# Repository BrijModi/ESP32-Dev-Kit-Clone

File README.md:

# ESP32 Dev Kit Clone

A custom **2-layer ESP32 Dev Kit V1 (30-pin)** PCB designed in **KiCad 9.0**. This repository contains the complete hardware design, including the schematic, PCB layout, 3D model, and Bill of Materials (BOM).

---

## Features

- ESP32-WROOM-32 module
- 2-layer PCB
- Micro USB interface
- USB-to-UART programming circuit
- Automatic Boot & Reset circuitry
- 3.3V power supply
- GPIO breakout headers
- Complete KiCad project files
- Interactive Bill of Materials
- 3D STEP model

---

## PCB Preview

### Front

### Back

---

## PCB Specifications

| Parameter | Value |
|-----------|-------|
| PCB Size | 47.02 × 29.16 mm |
| Layers | 2 |
| Software | KiCad 9.0 |

---

## 📂 Repository Contents

- `View/` – PCB renders, 3D model, schematic PDF, and PCB preview PDF.
- `ESP32 Dev Kit.kicad_pro` – KiCad project file.
- `ESP32 Dev Kit.kicad_sch` – Main schematic.
- `ESP32 Dev Kit.kicad_pcb` – PCB layout.
- `Connectors.kicad_sch` – Connector schematic sheet.
- `BOM.html` – Interactive Bill of Materials.
- `.gitignore` – Git ignore configuration.

---

## Documentation

- 📄 **Schematic:** [Schematic_View.pdf](View/Schematic_View.pdf)
- 📋 **Bill of Materials:** [BOM.html](BOM.html)
- 📦 **3D Model:** `View/ESP32 Dev Kit.step`

---

## Getting Started

1. Clone the repository

```bash
git clone https://github.com/BrijModi/ESP32-Dev-Kit-Clone.git
```

2. Open `ESP32 Dev Kit.kicad_pro` using **KiCad 9.0**.

---

# 📌 Applications

- ESP32 hardware reference
- PCB design learning
- Custom ESP32 development board
- Embedded systems projects
- Educational purposes

---

## License

This project is released under the **MIT License**.

---

## Author

**Brij Modi**

GitHub: https://github.com/BrijModi

⭐ If you found this project useful, consider starring the repository.

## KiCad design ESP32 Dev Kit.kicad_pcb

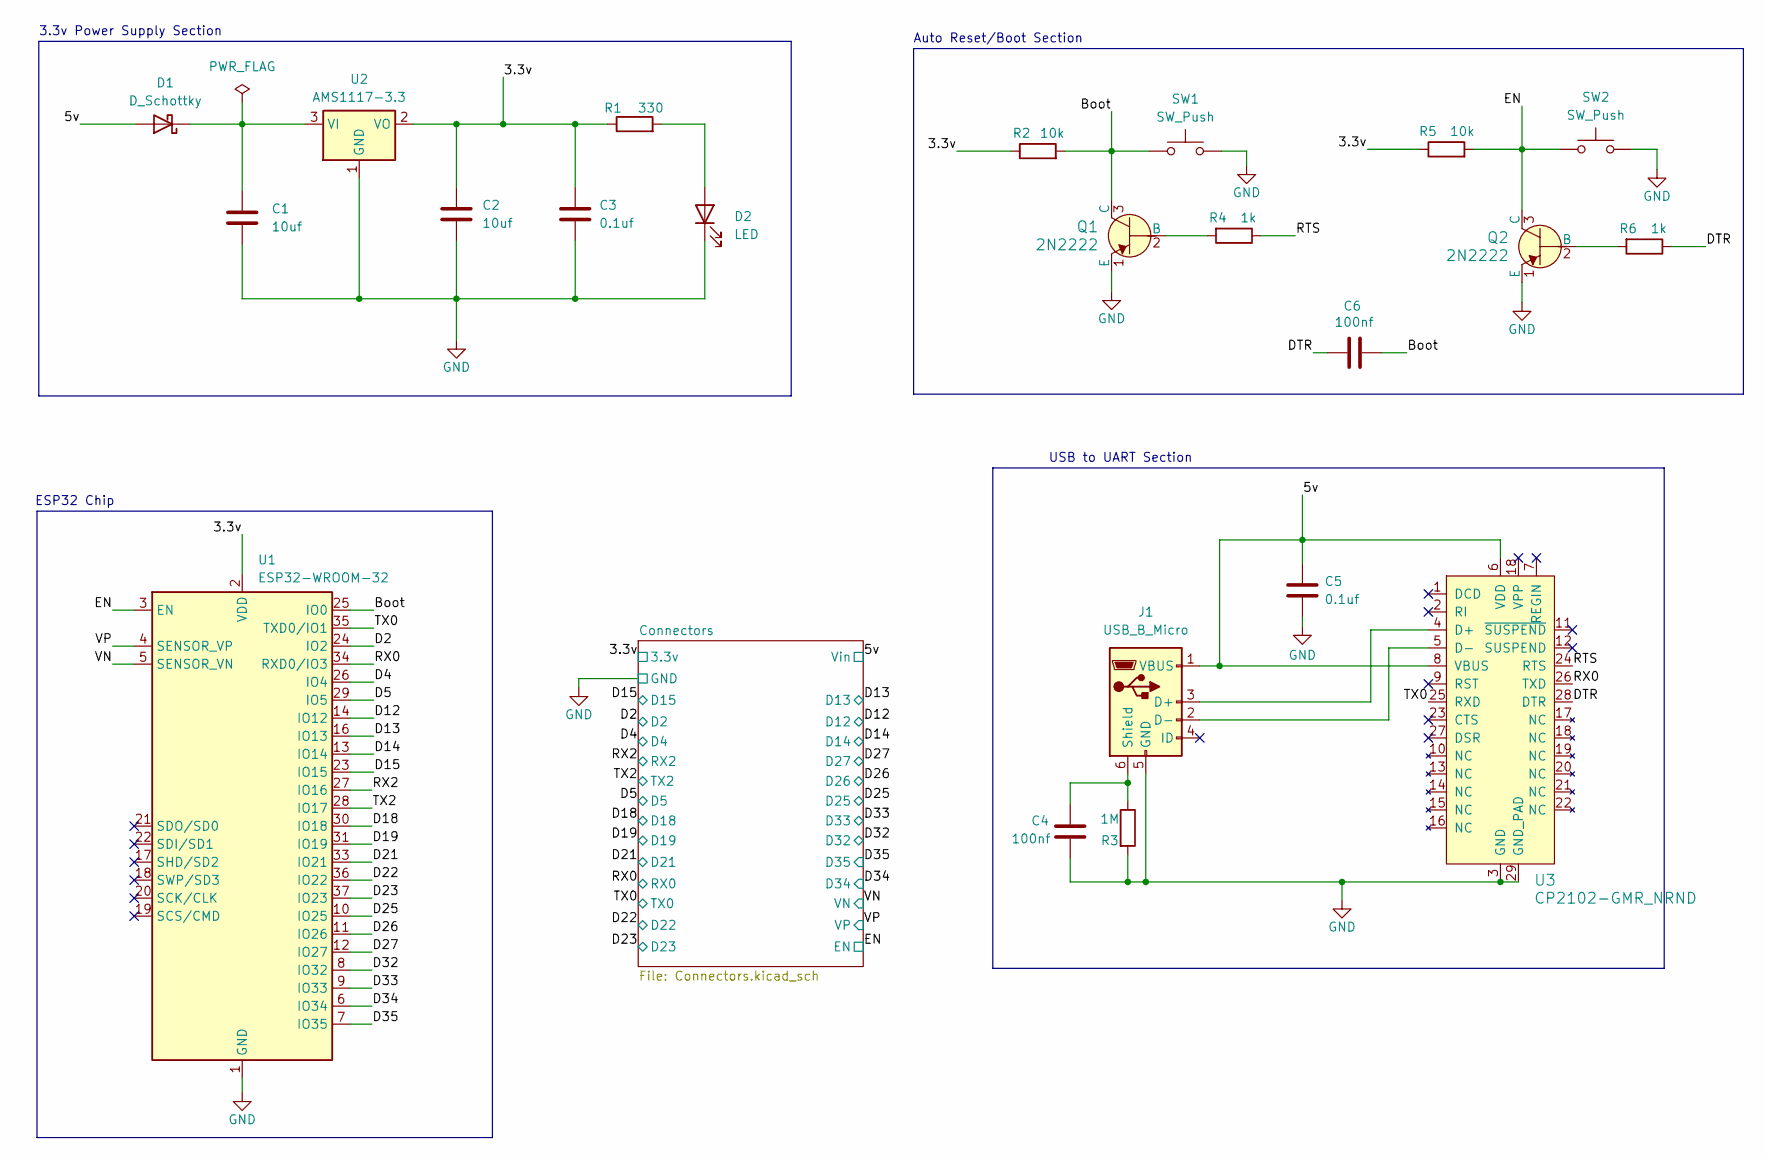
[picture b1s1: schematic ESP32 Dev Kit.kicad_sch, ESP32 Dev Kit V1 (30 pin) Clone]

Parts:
C1, C2: 10uf; C_0805_2012Metric_Pad1.18x1.45mm_HandSolder
C3, C5: 0.1uf; C_0805_2012Metric_Pad1.18x1.45mm_HandSolder
C4, C6: 100nf; C_0805_2012Metric_Pad1.18x1.45mm_HandSolder
D1: D_Schottky; D_SOD-123
D2: LED; LED_0805_2012Metric_Pad1.15x1.40mm_HandSolder
J1: USB_B_Micro; USB_Micro-B_Molex_47346-0001
Q1, Q2: 2N2222; SOT-23; MPN 2N2222; Digi-Key_PN 2N2222CS-ND
R1: 330; R_0805_2012Metric_Pad1.20x1.40mm_HandSolder
R2, R5: 10k; R_0805_2012Metric_Pad1.20x1.40mm_HandSolder
R3: 1M; R_0805_2012Metric_Pad1.20x1.40mm_HandSolder
R4, R6: 1k; R_0805_2012Metric_Pad1.20x1.40mm_HandSolder
SW1, SW2: SW_Push; SW_SPST_B3U-1000P
U1: ESP32-WROOM-32
U2: AMS1117-3.3; SOT-223-3_TabPin2
U3: CP2102-GMR_NRND; VFQFN-28-1EP_5x5mm; MPN CP2102-GMR; Digi-Key_PN 336-1160-1-ND

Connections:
/3.3v: C2.1, C3.1, R1.1, R2.1, R5.1, U1.2 (VDD), U2.2 (VO); also elsewhere on the board
/5v: C5.1, D1.2 (A), J1.1 (VBUS), U3.6 (VDD), U3.8 (VBUS); also elsewhere on the board
/Boot: C6.2, Q1.3 (C), R2.2, SW1.1, U1.25 (IO0)
/D2: U1.24 (IO2); also elsewhere on the board
/D4: U1.26 (IO4); also elsewhere on the board
/D5: U1.29 (IO5); also elsewhere on the board
/D12: U1.14 (IO12); also elsewhere on the board
/D13: U1.16 (IO13); also elsewhere on the board
/D14: U1.13 (IO14); also elsewhere on the board
/D15: U1.23 (IO15); also elsewhere on the board
/D18: U1.30 (IO18); also elsewhere on the board
/D19: U1.31 (IO19); also elsewhere on the board
/D21: U1.33 (IO21); also elsewhere on the board
/D22: U1.36 (IO22); also elsewhere on the board
/D23: U1.37 (IO23); also elsewhere on the board
/D25: U1.10 (IO25); also elsewhere on the board
/D26: U1.11 (IO26); also elsewhere on the board
/D27: U1.12 (IO27); also elsewhere on the board
/D32: U1.8 (IO32); also elsewhere on the board
/D33: U1.9 (IO33); also elsewhere on the board
/D34: U1.6 (IO34); also elsewhere on the board
/D35: U1.7 (IO35); also elsewhere on the board
/DTR: C6.1, R6.1, U3.28 (DTR)
/EN: Q2.3 (C), R5.2, SW2.1, U1.3 (EN); also elsewhere on the board
/RTS: R4.1, U3.24 (RTS)
/RX0: U1.34 (RXD0/IO3), U3.26 (TXD); also elsewhere on the board
/RX2: U1.27 (IO16); also elsewhere on the board
/TX0: U1.35 (TXD0/IO1), U3.25 (RXD); also elsewhere on the board
/TX2: U1.28 (IO17); also elsewhere on the board
/VN: U1.5 (SENSOR_VN); also elsewhere on the board
/VP: U1.4 (SENSOR_VP); also elsewhere on the board
GND: C1.2, C2.2, C3.2, C4.2, C5.2, D2.1 (K), J1.5 (GND), Q1.1 (E), Q2.1 (E), R3.2, SW1.2, SW2.2, U1.1 (GND), U1.15 (GND), U1.38 (GND), U1.39 (GND), U2.1 (GND), U3.3 (GND), U3.29 (GND_PAD); also elsewhere on the board
unnamed: C1.1, D1.1 (K), U2.3 (VI)
unnamed: D2.2 (A), R1.2
unnamed: J1.3 (D+), U3.4 (D+)
unnamed: J1.2 (D-), U3.5 (D-)
unnamed: C4.1, J1.6 (Shield), R3.1
unnamed: Q1.2 (B), R4.2
unnamed: Q2.2 (B), R6.2

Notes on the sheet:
Auto Reset/Boot Section
3.3v Power Supply Section
USB to UART Section
ESP32 Chip

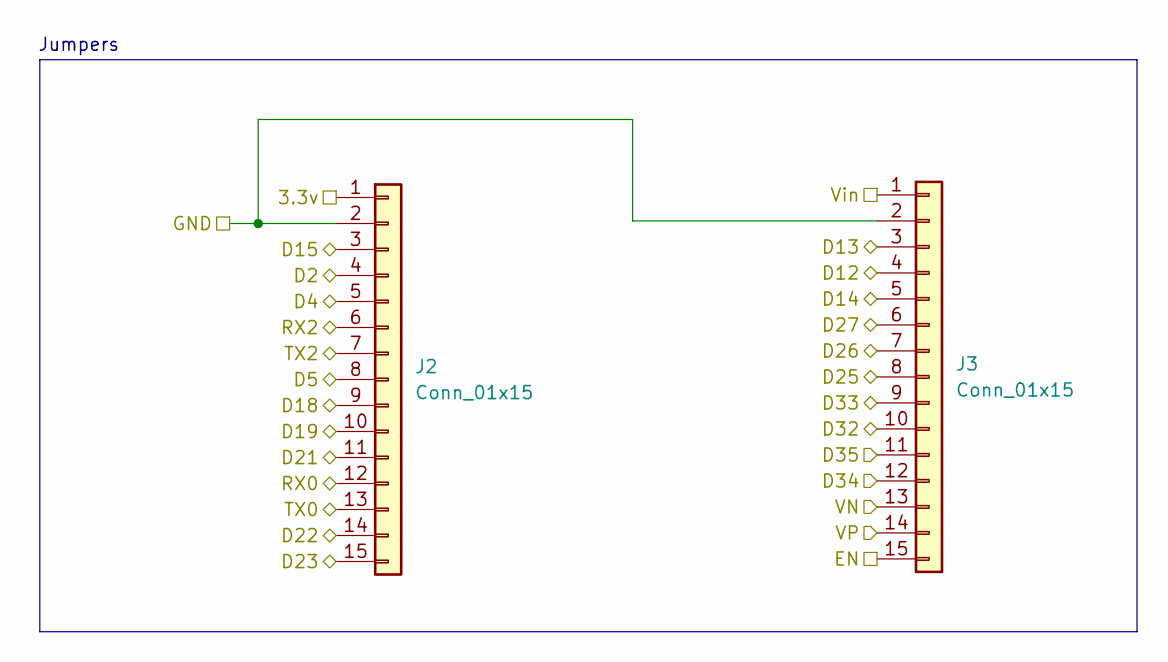
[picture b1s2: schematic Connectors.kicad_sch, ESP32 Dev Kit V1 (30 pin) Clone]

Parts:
J2, J3: Conn_01x15; PinHeader_1x15_P2.54mm_Vertical

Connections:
/3.3v: J2.1; also elsewhere on the board
/5v: J3.1; also elsewhere on the board
/D2: J2.4; also elsewhere on the board
/D4: J2.5; also elsewhere on the board
/D5: J2.8; also elsewhere on the board
/D12: J3.4; also elsewhere on the board
/D13: J3.3; also elsewhere on the board
/D14: J3.5; also elsewhere on the board
/D15: J2.3; also elsewhere on the board
/D18: J2.9; also elsewhere on the board
/D19: J2.10; also elsewhere on the board
/D21: J2.11; also elsewhere on the board
/D22: J2.14; also elsewhere on the board
/D23: J2.15; also elsewhere on the board
/D25: J3.8; also elsewhere on the board
/D26: J3.7; also elsewhere on the board
/D27: J3.6; also elsewhere on the board
/D32: J3.10; also elsewhere on the board
/D33: J3.9; also elsewhere on the board
/D34: J3.12; also elsewhere on the board
/D35: J3.11; also elsewhere on the board
/EN: J3.15; also elsewhere on the board
/RX0: J2.12; also elsewhere on the board
/RX2: J2.6; also elsewhere on the board
/TX0: J2.13; also elsewhere on the board
/TX2: J2.7; also elsewhere on the board
/VN: J3.13; also elsewhere on the board
/VP: J3.14; also elsewhere on the board
GND: J2.2, J3.2; also elsewhere on the board

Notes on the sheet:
Jumpers

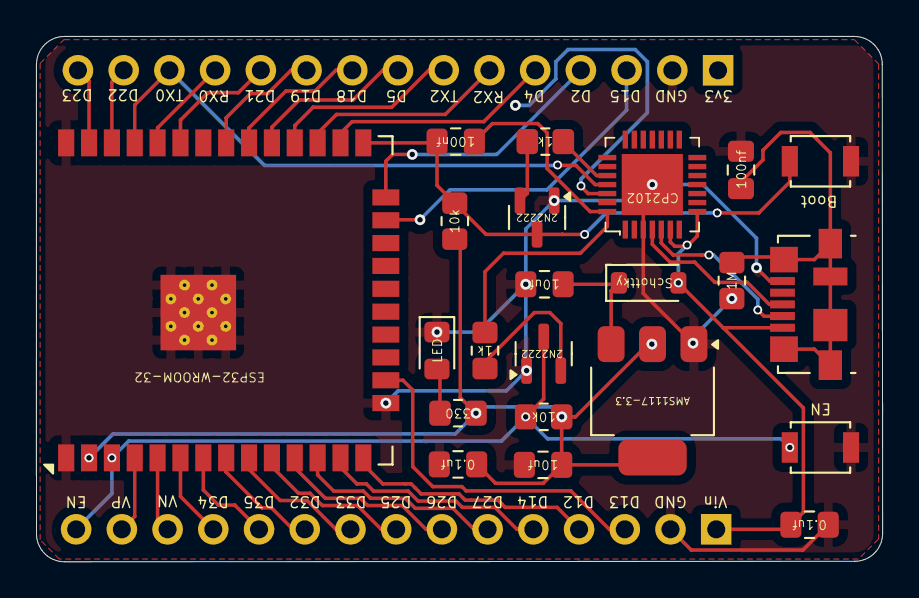
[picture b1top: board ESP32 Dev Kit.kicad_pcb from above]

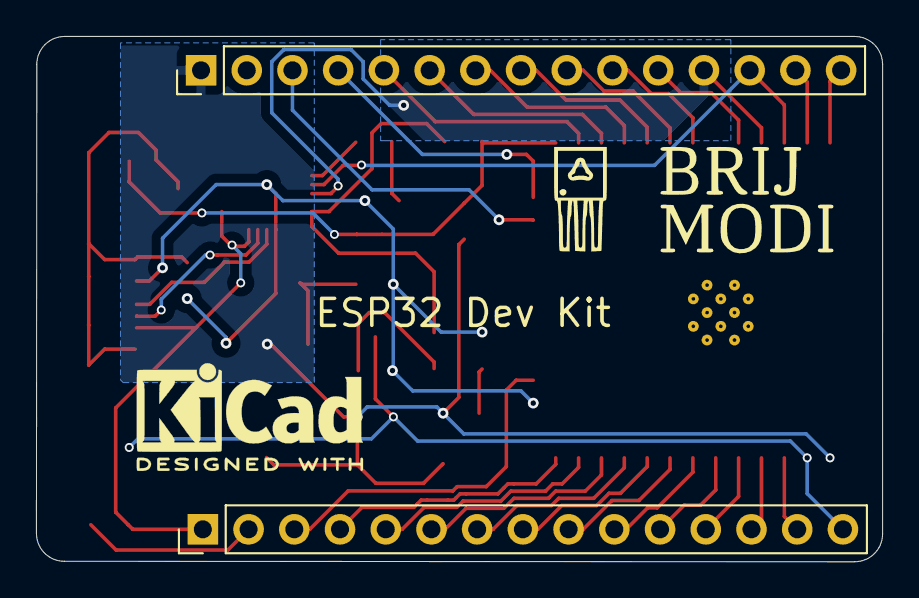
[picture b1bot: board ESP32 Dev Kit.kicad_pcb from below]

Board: 2 copper layers, 47.0 x 29.2 mm, 24 parts (2 on the bottom side), 39 nets.

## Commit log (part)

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2025-04-13 Power Supply Section
2025-04-13 Added USB to UART Section
2025-04-13 ESP32 Chip and Auto Reset/Boot Sections Added
2025-04-14 Added Jumpers Section
2025-04-14 Added Footprints to the Symbols
2025-04-15 Schematic and Footprints Revised
2025-04-15 Footprints placed & Revised
2025-04-15 Added Traces to the PCB - R1
2025-04-16 PCB Revised
2025-04-16 Final PCB
2025-04-16 Final PCB with view
2025-04-16 Added BOM
